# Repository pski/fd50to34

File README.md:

# fd50to34: Adapt 34 Pin Floppy Drives to 50 Pin Controllers
## by Mark J. Blair <nf6x@nf6x.net>

This board is a cable adapter to allow 3.5" or 5.25" floppy disk drives to be connected to computer systems with floppy disk controllers that are designed for use with 8" floppy disk drives. It is inspired by instructions by Frank Durda IV for connecting 5.25" floppy disk drives to Radio Shack/Tandy model II, 12, 16 and 6000 computers, as found at this URL:

http://nemesis.lonestar.org/computers/tandy/hardware/model16_6000/floppyfix.html

## Features

* Jumper-selectable double-sided disk support.
* Jumper selection allows drive motors to be strapped on all the time, or controlled by either the head load or in-use/door-lock signal.
* Bank of shorted resistor footprints allows easy drive select number remapping.
* Drive signals are labeled on bottom of board for debugging purposes.

## Schematic Diagram

## JP1: Double-Sided Media Detect

Install a jumper at JP1 to enable double-sided disk support. If any single-sided disks will be used, remove this jumper while accessing them, since installing this jumper makes the controller think that all drives are reporting double-sided media.

If desired, connect a remote SPST switch to this jumper, and close it to enable double-sided media.

## JP2 and JP3: Motor Control

Frank recommends strapping the motor control line to ground to force the drive motors on, since 8" drive motor control works differently than 3.5" and 5.25" drive interfaces expect. To get this behavior, install a jumper between pins 2 and 3 of JP3 (labeled MTRON and GND on the PCB). JP2 is ignored in this configuration.

Some drives can be configured to qualify their motor controls with the drive select signals. With these drives, you may wish to experiment with different motor control schemes. To enable these schemes, first move the jumper on JP3 to pins 1 and 2. Then, install a jumper on JP2 to connect the motor control signal to either the head load signal or the door lock signal.

When connecting a Lotharek floppy drive emulator to a TRS-80 Model II/12/16/6000, the door lock signal seems to work well for drive motor control. For this configuration, install a jumper between pins 1 and 2 of JP2, and another jumper between pins 1 and 2 of JP3.

## JP4: Density Select

Some floppy drives use J2 pin 2 to select different density modes. On compatible 3.5" drives, pulling this pin down will select a 360 RPM mode which may work well on systems expecting 8" floppy drives. To do this, install a jumper between pins 2 and 3 of JP4. Install no jumper on JP4 for default behavior.

Installing a jumper between pins 1 and 2 connects the reduced write current signal on the 8" interface to J2 pin 2, which is also used to select reduced write current on some 5.25" drives. This option is experimental. 

## R1-R4: Drive Select Remapping

If you need to remap the drive select signals, first cut the exposed traces on the top side of the board which short out resistors R1 through R4 (which are not normally installed). Then, solder wires between the pads of R1-R4 to map the drive select signals as needed.

## Suggested Parts

Refs    | Manufacturer | Part Number  | Comments
--------|--------------|--------------|---------------
J1      | Wurth        | 61205022121  |
J2      | Wurth        | 61203422121  |
JP1-JP4 | Sullins      | PBC36SBAN    | Cut to length
Jumpers | Sullins      | QPC02SXGN-RC |

## About the Design

This board was designed in Kicad 2014-12-16 BZR 5324 on a Mac.
Design rules are 6 mil line, 6 mil trace, 13 mil via hole. It is suitable for fabrication at OSH Park.

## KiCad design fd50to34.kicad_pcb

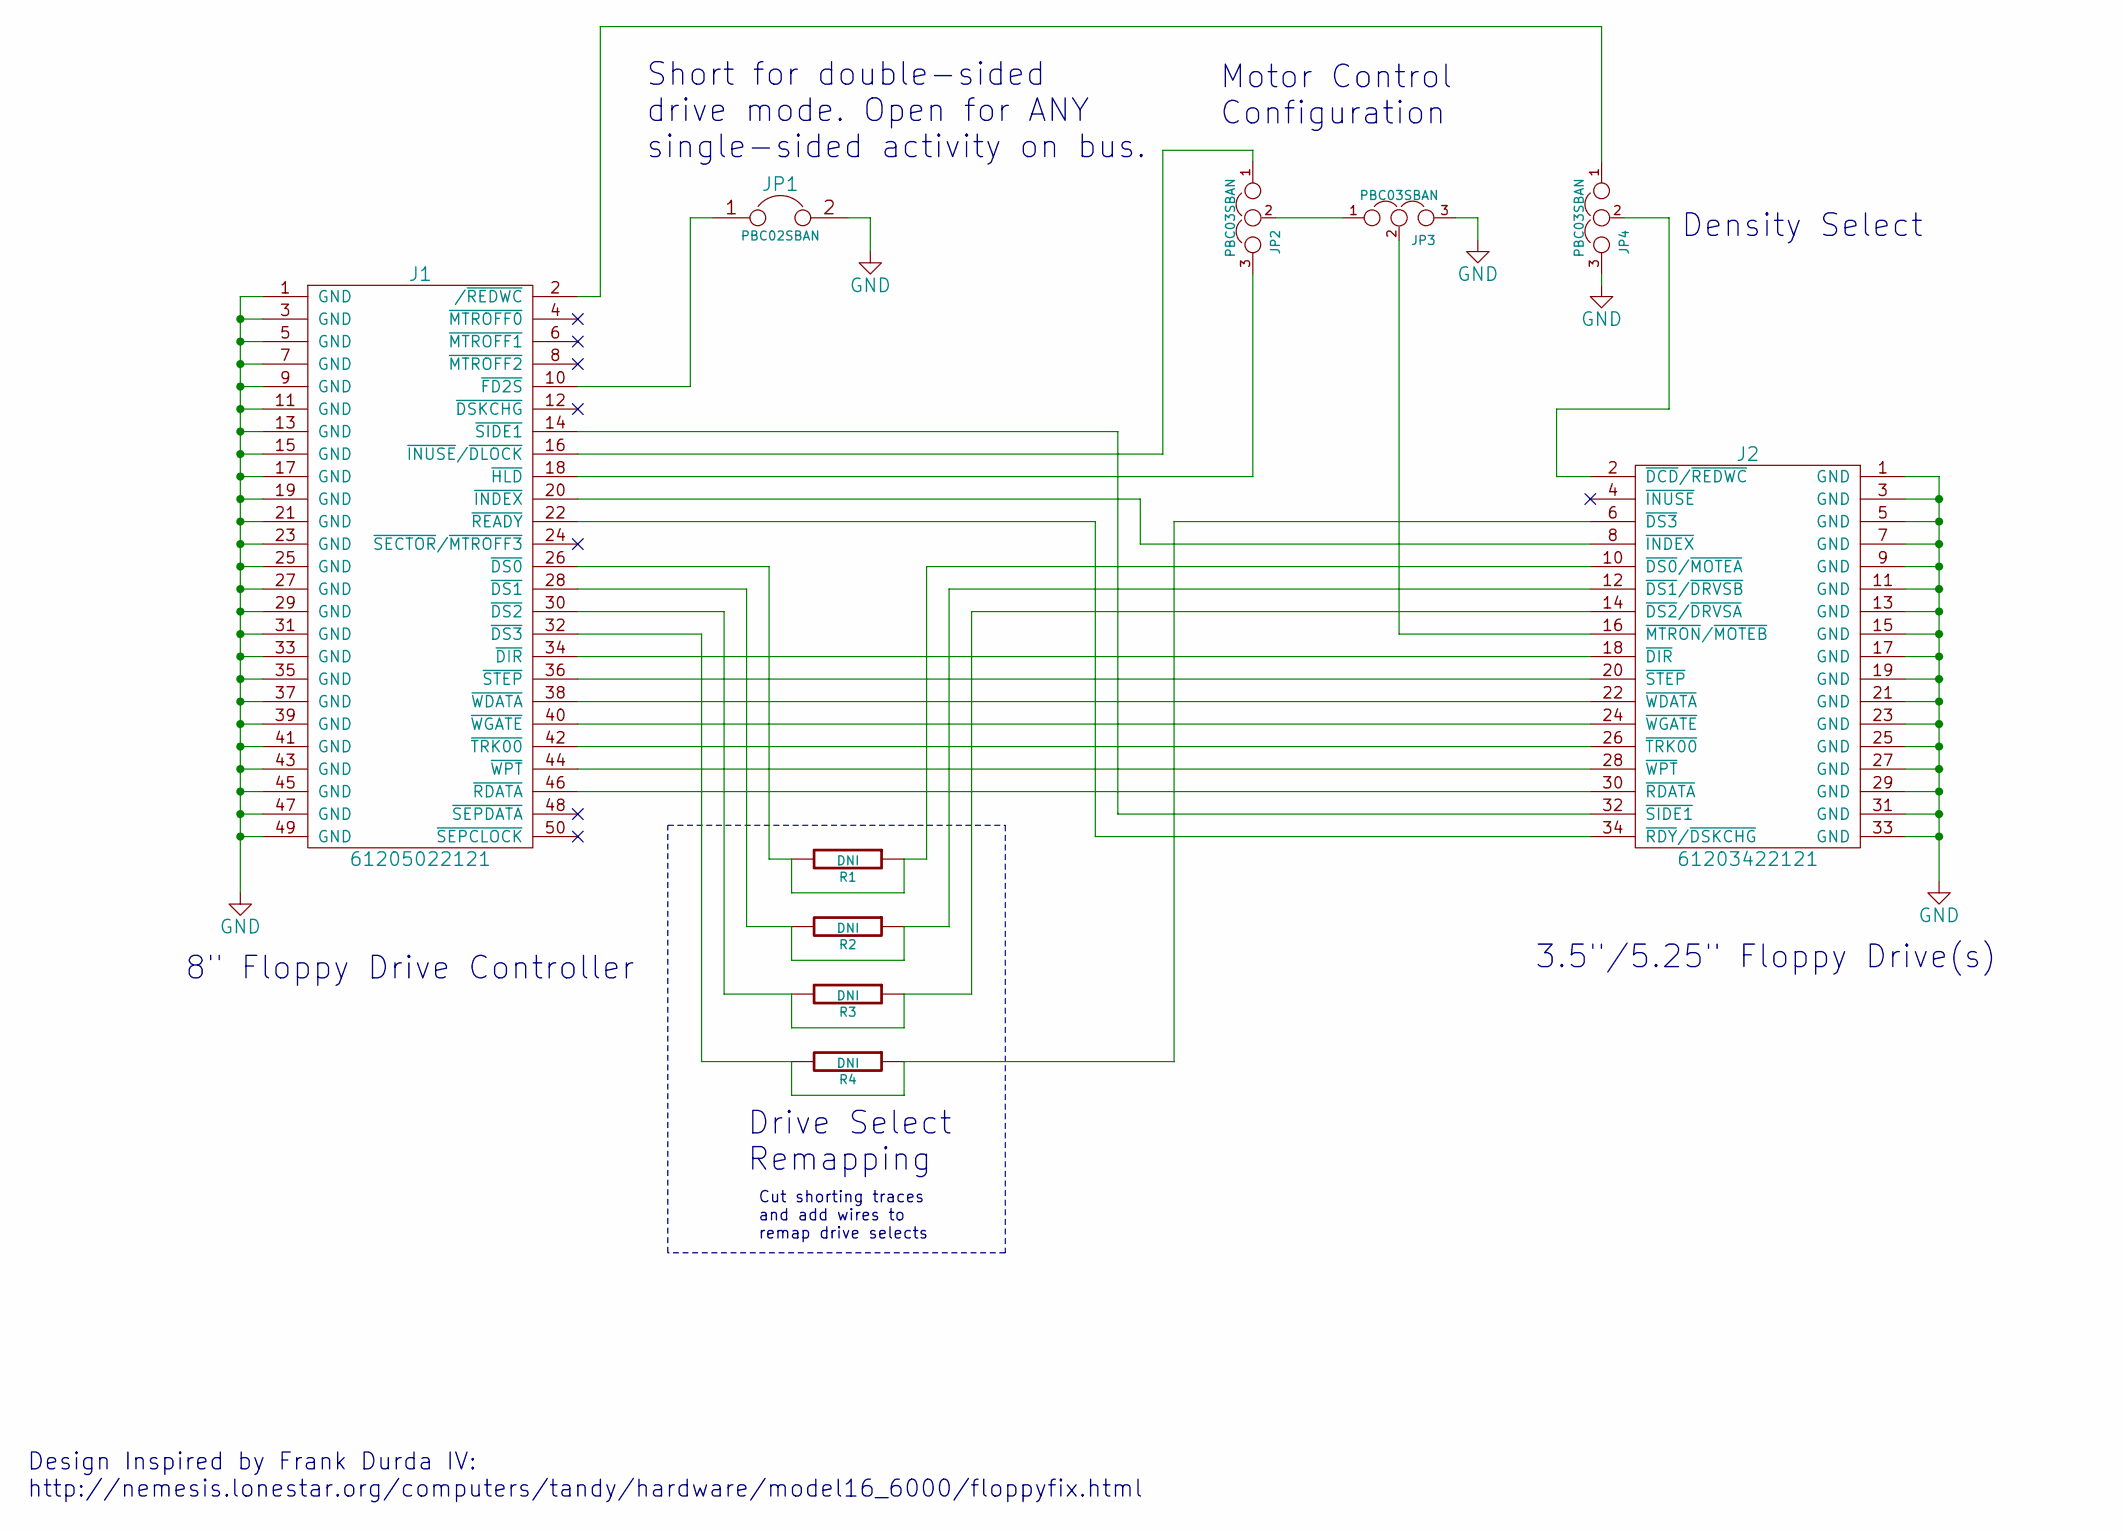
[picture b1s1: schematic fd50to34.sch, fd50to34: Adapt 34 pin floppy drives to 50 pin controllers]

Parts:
J1: 61205022121; Wurth_61205022121; PartNum 61205022121
J2: 61203422121; Wurth_61203422121; PartNum 61203422121
JP1: PBC02SBAN; Pin_Header_Angled_1x02
JP2, JP3, JP4: PBC03SBAN; Pin_Header_Angled_1x03
R1, R2, R3, R4: DNI; Resistor_Horizontal_RM10mm

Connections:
GND: J1.1 (GND), J1.3 (GND), J1.5 (GND), J1.7 (GND), J1.9 (GND), J1.11 (GND), J1.13 (GND), J1.15 (GND), J1.17 (GND), J1.19 (GND), J1.21 (GND), J1.23 (GND), J1.25 (GND), J1.27 (GND), J1.29 (GND), J1.31 (GND), J1.33 (GND), J1.35 (GND), J1.37 (GND), J1.39 (GND), J1.41 (GND), J1.43 (GND), J1.45 (GND), J1.47 (GND), J1.49 (GND), J2.1 (GND), J2.3 (GND), J2.5 (GND), J2.7 (GND), J2.9 (GND), J2.11 (GND), J2.13 (GND), J2.15 (GND), J2.17 (GND), J2.19 (GND), J2.21 (GND), J2.23 (GND), J2.25 (GND), J2.27 (GND), J2.29 (GND), J2.31 (GND), J2.33 (GND), JP1.2, JP3.3, JP4.3
unnamed: J1.2 (/~REDWC), JP4.1
unnamed: J1.10 (~FD2S), JP1.1
unnamed: J1.14 (~SIDE1), J2.32 (~SIDE1)
unnamed: J1.16 (~INUSE~/~DLOCK), JP2.1
unnamed: J1.18 (~HLD), JP2.3
unnamed: J1.20 (~INDEX), J2.8 (~INDEX)
unnamed: J1.22 (~READY), J2.34 (~RDY~/~DSKCHG)
unnamed: J1.26 (~DS0), J2.10 (~DS0~/~MOTEA), R1.1, R1.2
unnamed: J1.28 (~DS1), J2.12 (~DS1~/~DRVSB), R2.1, R2.2
unnamed: J1.30 (~DS2), J2.14 (~DS2~/~DRVSA), R3.1, R3.2
unnamed: J1.32 (~DS3), J2.6 (~DS3), R4.1, R4.2
unnamed: J1.34 (~DIR), J2.18 (~DIR)
unnamed: J1.36 (~STEP), J2.20 (~STEP)
unnamed: J1.38 (~WDATA), J2.22 (~WDATA)
unnamed: J1.40 (~WGATE), J2.24 (~WGATE)
unnamed: J1.42 (~TRK00), J2.26 (~TRK00)
unnamed: J1.44 (~WPT), J2.28 (~WPT)
unnamed: J1.46 (~RDATA), J2.30 (~RDATA)
unnamed: J2.2 (~DCD~/~REDWC), JP4.2
unnamed: J2.16 (~MTRON~/~MOTEB), JP3.2
unnamed: JP2.2, JP3.1

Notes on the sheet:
8" Floppy Drive Controller
3.5"/5.25" Floppy Drive(s)
Short for double-sided drive mode. Open for ANY single-sided activity on bus.
Motor Control Configuration
Drive Select Remapping
Design Inspired by Frank Durda IV: http://nemesis.lonestar.org/computers/tandy/hardware/model16_6000/floppyfix.html
Cut shorting traces and add wires to remap drive selects
Density Select

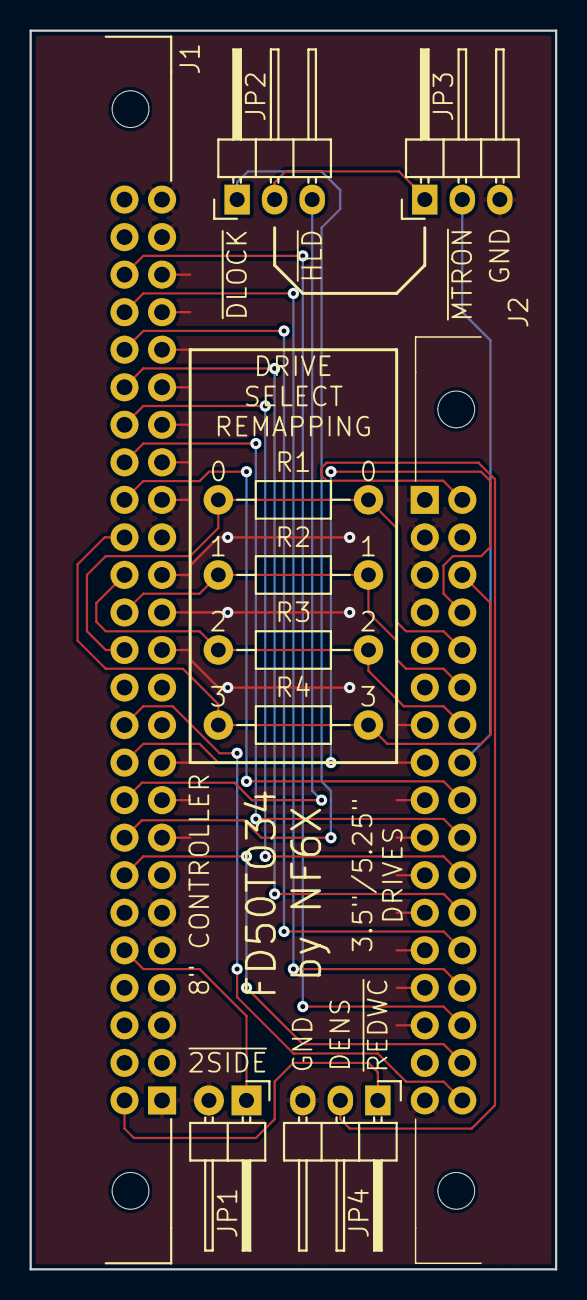
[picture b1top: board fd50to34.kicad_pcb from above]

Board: 2 copper layers, 35.6 x 83.8 mm, 10 parts (0 on the bottom side), 22 nets.

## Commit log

2015-07-06 Initial commit.
2015-07-06 Added PCB renderings.
2015-07-06 Added documentation and license info.
2015-07-06 Typo correction
2015-07-06 Added reference to schematic diagram.
2015-07-06 Added PNG version of schematic for inline display in README.md.
2015-07-06 Corrected gerber origin.
2015-07-06 Added errata and changelog file. Corrected top silkscreen typo on PCB. Incremented PCB version to v2. Updated schematic version to 2.0-DRAFT.
2015-07-07 Added library cache and BOM XML file to repo.
2015-07-31 Added density select jumper.
2015-08-19 Revised part numbers for production quote at MacroFab.
2015-08-31 Corrected project name in COPYING file.
2015-09-22 Removed OSHW logo.
2015-09-22 Schematic PNG regenerated.
2015-09-22 Fixed bad drill file configuration settings.
